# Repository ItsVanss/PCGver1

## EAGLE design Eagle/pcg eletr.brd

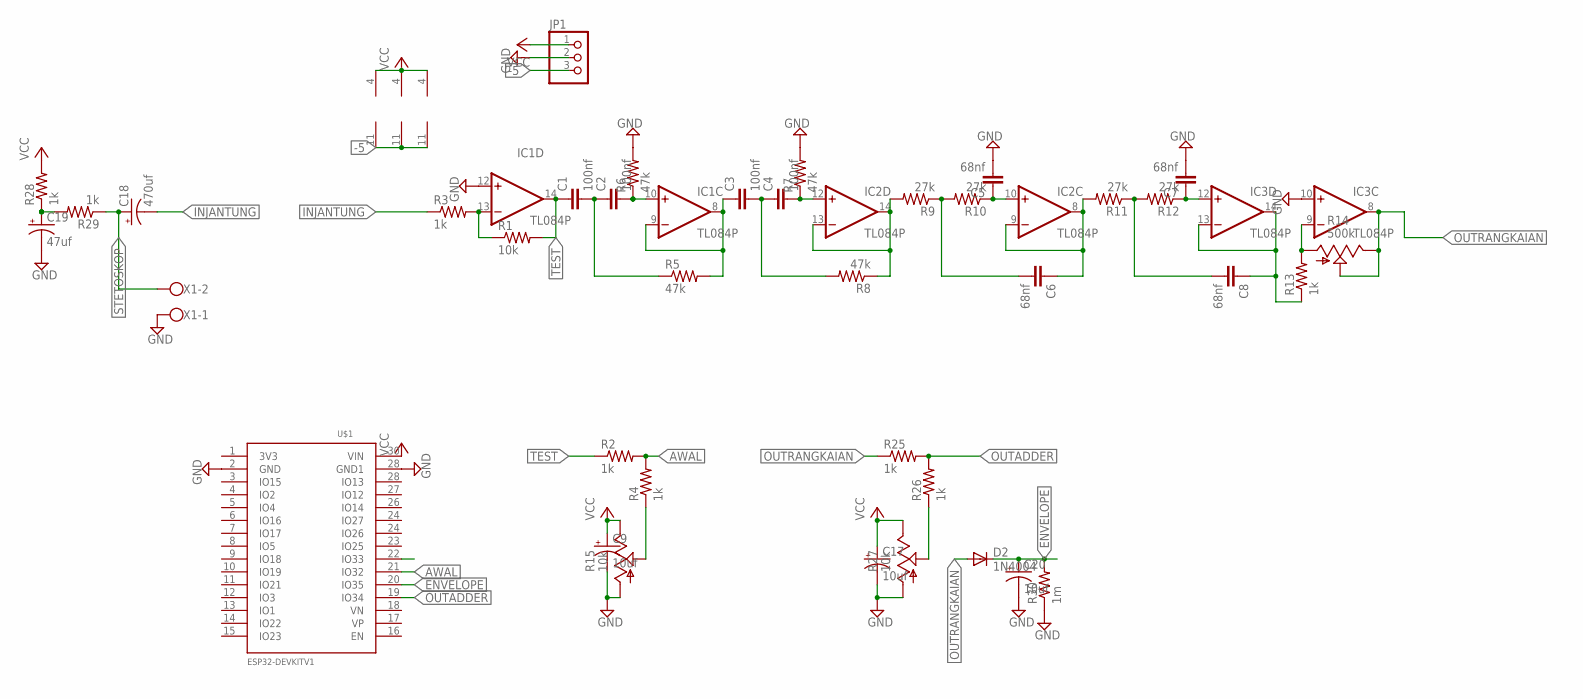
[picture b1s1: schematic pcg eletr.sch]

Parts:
C1, C2, C3, C4: 100nf; C050-025X075
C5, C6, C7, C8: 68nf; C050-025X075
C9, C17, C20: 10uf; E2-5
C18: 470uf; E2,5-7
C19: 47uf; E2-5
D2: 1N4004; DO41-10
IC1, IC2, IC3: TL084P; DIL14
JP1: PINHD-1X3; 1X03
R1: 10k; 0207/7
R2, R3, R4, R13, R25, R26, R28, R29: 1k; 0207/7
R5, R6, R7, R8: 47k; 0207/7
R9, R10, R11, R12: 27k; 0207/7
R14: 500k; B64Y
R15, R27: 10k; B64Y
R30: 1m; 0207/7
U$1: ESP32DEVKITV1; ESP32-DEVKITV1
X1: W237-102

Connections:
-5: IC1.11 (V-), IC2.11 (V-), IC3.11 (V-), JP1.3
AWAL: R2.2, R4.2, U$1.21 (IO32)
ENVELOPE: C20.+, D2.C, R30.2, U$1.20 (IO35)
GND: C5.2, C7.2, C9.-, C17.-, C19.-, C20.-, IC1.12 (+IN), IC3.10 (+IN), JP1.2, R6.2, R7.2, R15.A, R27.A, R30.1, U$1.2 (GND), U$1.28 (IO13), X1.1
INJANTUNG: C18.-, R3.1
unnamed: IC1.13 (-IN), R1.1, R3.2
unnamed: R4.1, R15.S
unnamed: C1.2, C2.1, R5.1
unnamed: C2.2, IC1.10 (+IN), R6.1
unnamed: C3.1, IC1.8 (OUT), IC1.9 (-IN), R5.2
unnamed: C3.2, C4.1, R8.2
unnamed: C4.2, IC2.12 (+IN), R7.1
unnamed: IC2.13 (-IN), IC2.14 (OUT), R8.1, R9.2
unnamed: C6.2, R9.1, R10.2
unnamed: C5.1, IC2.10 (+IN), R10.1
unnamed: C6.1, IC2.8 (OUT), IC2.9 (-IN), R11.2
unnamed: C8.2, R11.1, R12.2
unnamed: C7.1, IC3.12 (+IN), R12.1
unnamed: C8.1, IC3.13 (-IN), IC3.14 (OUT), R13.1
unnamed: IC3.9 (-IN), R13.2, R14.A
unnamed: R26.1, R27.S
unnamed: C19.+, R28.1, R29.2
OUTADDER: R25.2, R26.2, U$1.19 (IO34)
OUTRANGKAIAN: D2.A, IC3.8 (OUT), R14.E, R14.S, R25.1
STETOSKOP: C18.+, R29.1, X1.2
TEST: C1.1, IC1.14 (OUT), R1.2, R2.1
VCC: C9.+, C17.+, IC1.4 (V+), IC2.4 (V+), IC3.4 (V+), JP1.1, R15.E, R27.E, R28.2, U$1.30 (VIN)

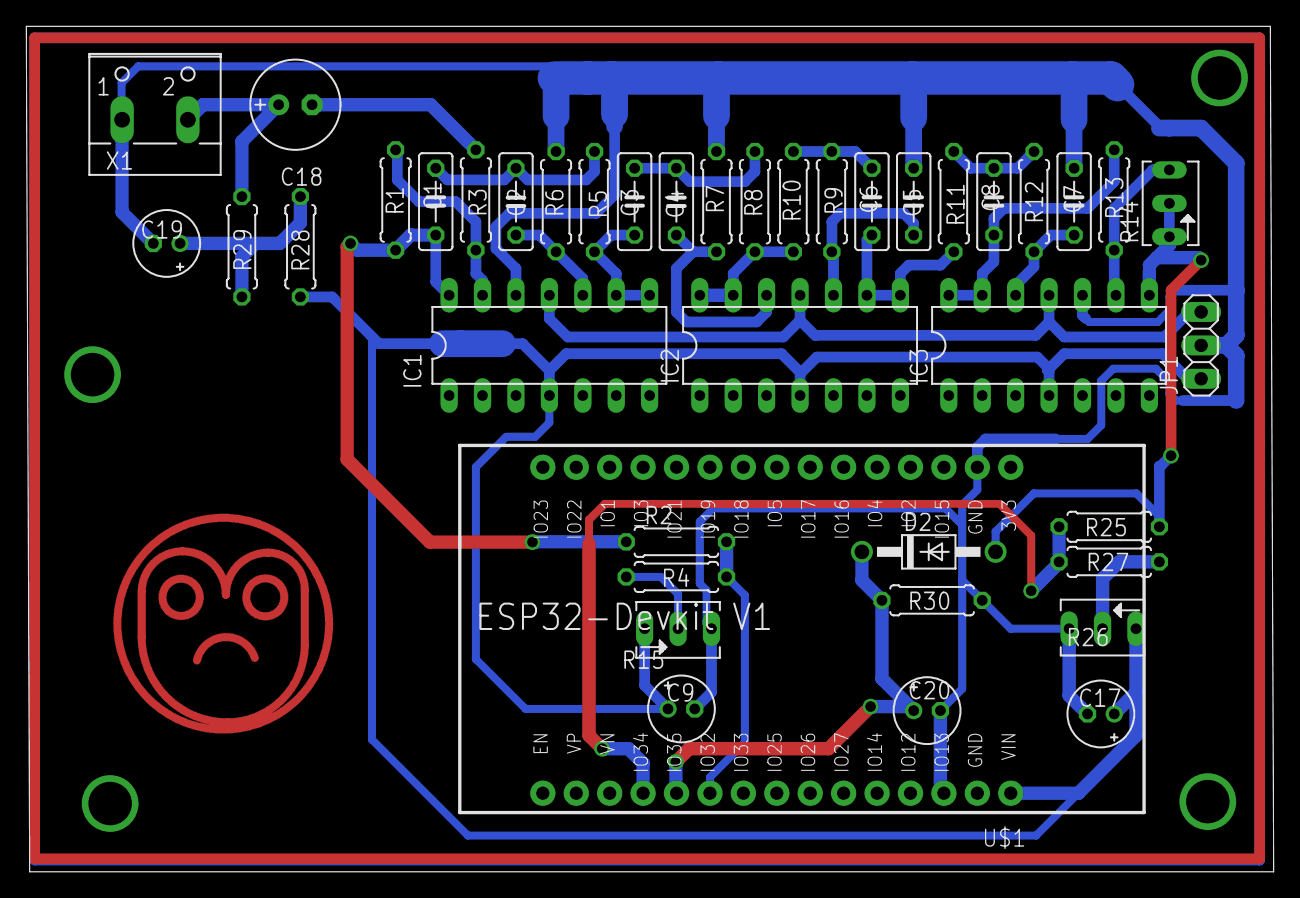
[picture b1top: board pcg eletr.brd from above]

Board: 2 copper layers, 94.8 x 64.3 mm, 41 parts (0 on the bottom side), 27 nets.

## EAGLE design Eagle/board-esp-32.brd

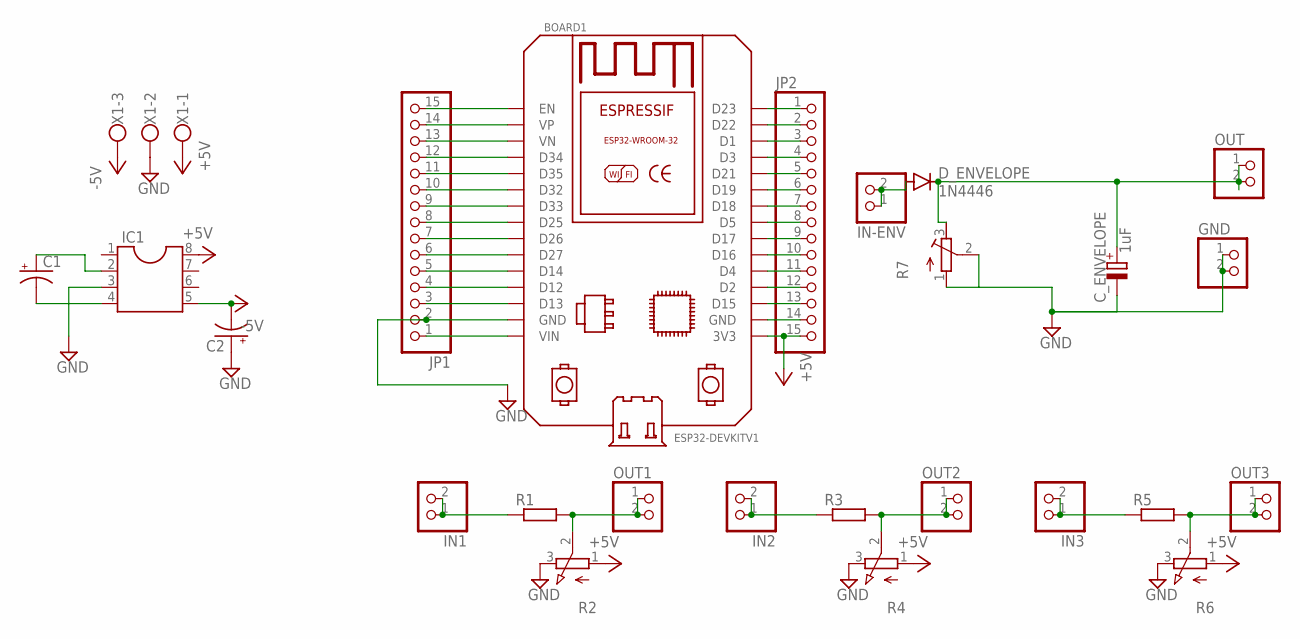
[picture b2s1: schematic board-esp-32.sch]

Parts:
BOARD1: ESP32DEVKITV1; ESP32-DEVKITV1
C1, C2: CPOL-USE2.5-5; E2,5-5
C_ENVELOPE: 1uF; E2,5-6
D_ENVELOPE: 1N4446; DO35-10
GND: PINHD-1X2; 1X02
IC1: DIL8S; SOCKET-08
IN1, IN2, IN3: PINHD-1X2; 1X02
IN-ENV: PINHD-1X2; 1X02
JP1, JP2: PINHD-1X15; 1X15
OUT, OUT1, OUT2, OUT3: PINHD-1X2; 1X02
R1, R3, R5: R-EU_0207/10; 0207/10
R2, R4, R6: 3RP/1610N
R7: R-TRIMM3339P; RTRIM3339P
X1: W237-103

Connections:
+5V: BOARD1.3V3, IC1.8, JP2.15, R2.1 (A), R4.1 (A), R6.1 (A), X1.1
-5V: C2.-, IC1.5, X1.3
GND: BOARD1.GND, C2.+, C_ENVELOPE.-, GND.1, GND.2, IC1.3, JP1.2, R2.3 (E), R4.3 (E), R6.3 (E), R7.1 (A), R7.2 (S), X1.2
unnamed: IN1.1, IN1.2, R1.1
unnamed: OUT1.1, OUT1.2, R1.2, R2.2 (S)
unnamed: IN2.1, IN2.2, R3.1
unnamed: OUT2.1, OUT2.2, R3.2, R4.2 (S)
unnamed: IN3.1, IN3.2, R5.1
unnamed: OUT3.1, OUT3.2, R5.2, R6.2 (S)
unnamed: BOARD1.GND@1 (GND), JP2.14
unnamed: C1.+, IC1.2
unnamed: C1.-, IC1.4
unnamed: BOARD1.D15, JP2.13
unnamed: BOARD1.D2, JP2.12
unnamed: BOARD1.D4, JP2.11
unnamed: BOARD1.D16, JP2.10
unnamed: BOARD1.D17, JP2.9
unnamed: BOARD1.D5, JP2.8
unnamed: C_ENVELOPE.+, D_ENVELOPE.C, OUT.1, OUT.2, R7.3 (E)
unnamed: D_ENVELOPE.A, IN-ENV.1, IN-ENV.2
unnamed: BOARD1.D18, JP2.7
unnamed: BOARD1.D19, JP2.6
unnamed: BOARD1.D21, JP2.5
unnamed: BOARD1.D3, JP2.4
unnamed: BOARD1.D1, JP2.3
unnamed: BOARD1.D22, JP2.2
unnamed: BOARD1.D23, JP2.1
unnamed: BOARD1.EN, JP1.15
unnamed: BOARD1.VP, JP1.14
unnamed: BOARD1.VN, JP1.13
unnamed: BOARD1.D34, JP1.12
unnamed: BOARD1.D35, JP1.11
unnamed: BOARD1.D32, JP1.10
unnamed: BOARD1.D33, JP1.9
unnamed: BOARD1.D25, JP1.8
unnamed: BOARD1.D26, JP1.7
unnamed: BOARD1.D27, JP1.6
unnamed: BOARD1.D14, JP1.5
unnamed: BOARD1.D12, JP1.4
unnamed: BOARD1.D13, JP1.3
unnamed: BOARD1.VIN, JP1.1

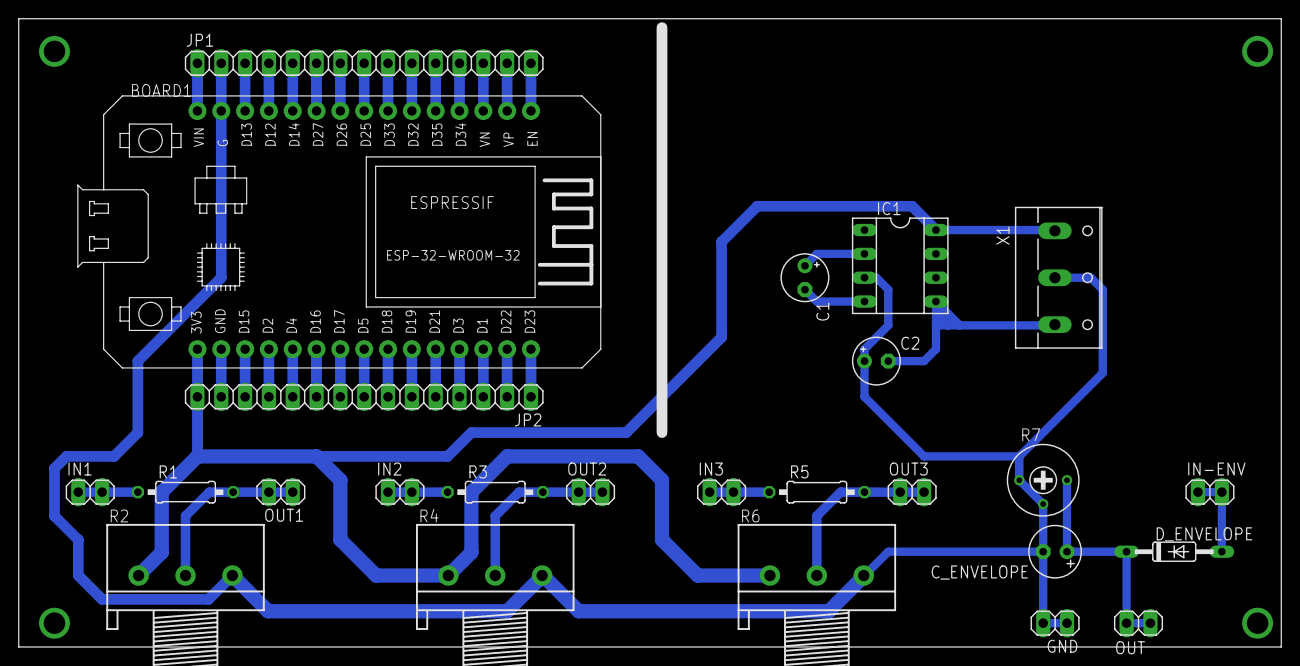
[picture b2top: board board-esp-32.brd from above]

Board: 2 copper layers, 134.6 x 67.0 mm, 25 parts (0 on the bottom side), 41 nets.

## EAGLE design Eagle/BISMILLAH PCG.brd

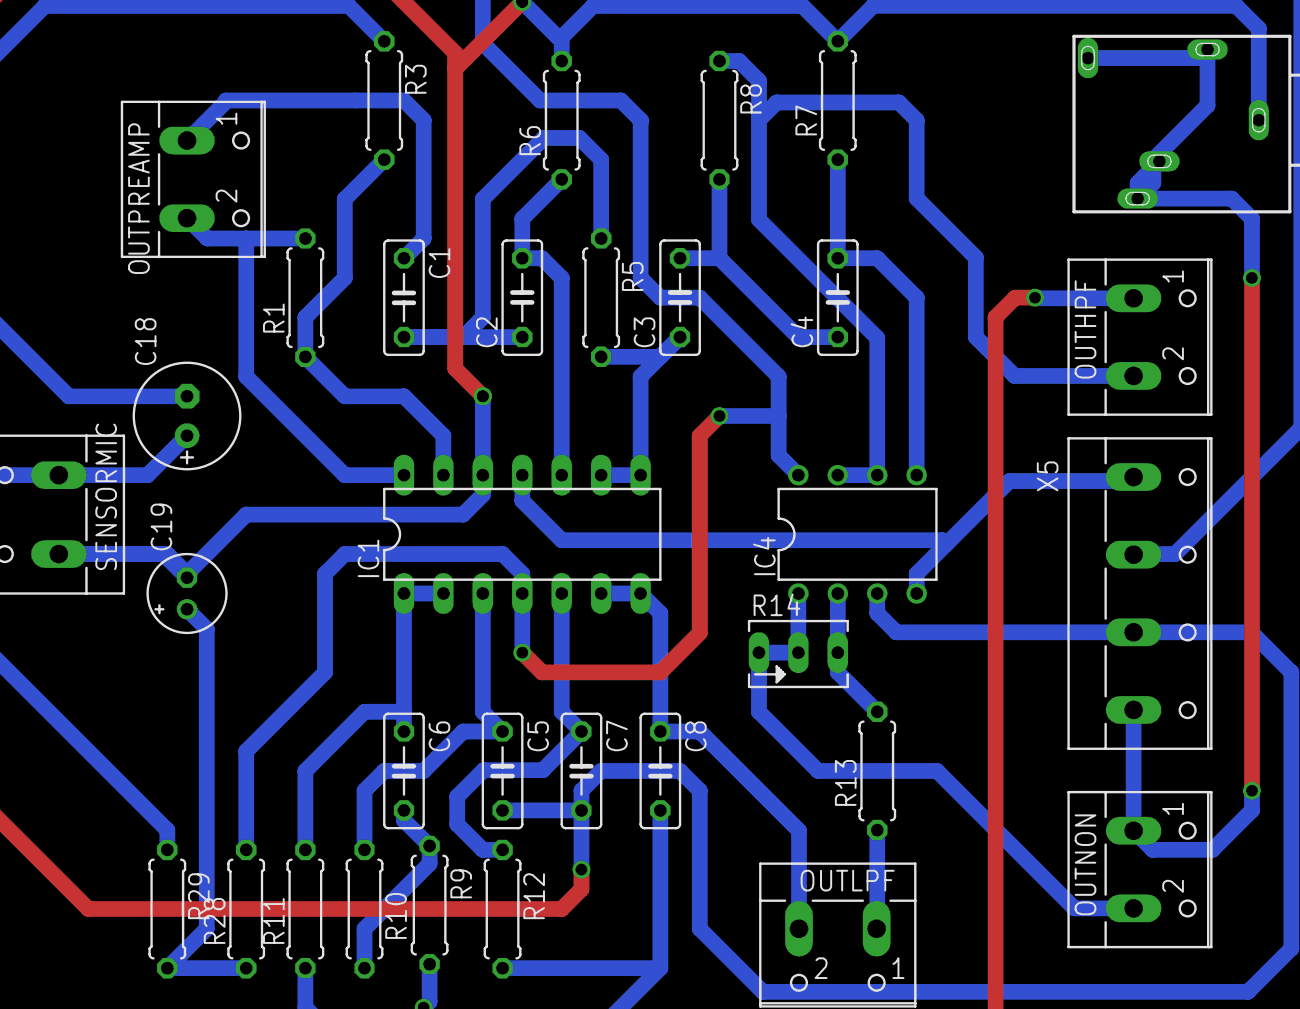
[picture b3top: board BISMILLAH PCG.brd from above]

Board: 2 copper layers, 33 parts (0 on the bottom side), 26 nets.

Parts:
C1, C2, C3, C4: 100nf; C050-025X075
C5, C6, C7, C8: 68nf; C050-025X075
C18: 470uf; E2,5-7
C19: 47uf; E2-5
HEADSET: headset; 1503_09
IC1: TL084P; DIL14
IC4: TL082P; DIL08
OUTHPF: W237-102
OUTLPF: W237-102
OUTNON: W237-102
OUTPREAMP: W237-102
R1: 10k; 0207/7
R3, R13, R28, R29: 1k; 0207/7
R5, R6, R7, R8: 47k; 0207/7
R9, R10, R11, R12: 27k; 0207/7
R14: 500k; B64Y
SENSORMIC: W237-132
X5: W237-4

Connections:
GND: C5.2, C7.2, C19.-, HEADSET.1, IC1.12, IC4.3, R6.2, R7.2, SENSORMIC.1, X5.3
unnamed: IC1.13, R1.1, R3.2
unnamed: IC1.14, OUTPREAMP.2, R1.2
unnamed: C18.-, R3.1
unnamed: C1.1, OUTPREAMP.1
unnamed: IC4.1, OUTNON.2, R14.E, R14.S
unnamed: C1.2, C2.1, R5.1
unnamed: C2.2, IC1.10, R6.1
unnamed: C3.1, IC1.8, IC1.9, R5.2
unnamed: C3.2, C4.1, R8.2
unnamed: C4.2, IC4.5, R7.1
unnamed: IC4.6, IC4.7, OUTHPF.2, R8.1
unnamed: C6.2, R9.1, R10.2
unnamed: C5.1, IC1.3, R10.1
unnamed: C6.1, IC1.1, IC1.2, R11.2
unnamed: C8.2, R11.1, R12.2
unnamed: C7.1, IC1.5, R12.1
unnamed: C8.1, IC1.6, IC1.7, OUTLPF.2
unnamed: IC4.2, R13.2, R14.A
unnamed: OUTHPF.1, R9.2
unnamed: OUTLPF.1, R13.1
unnamed: C19.+, R28.1, R29.2
OUTJANTUNG: HEADSET.2, HEADSET.3, HEADSET.4, HEADSET.5, OUTNON.1, X5.4
STETOSKOP1: C18.+, R29.1, SENSORMIC.2
V-: IC1.11, IC4.4, X5.1
VCC: IC1.4, IC4.8, R28.2, X5.2

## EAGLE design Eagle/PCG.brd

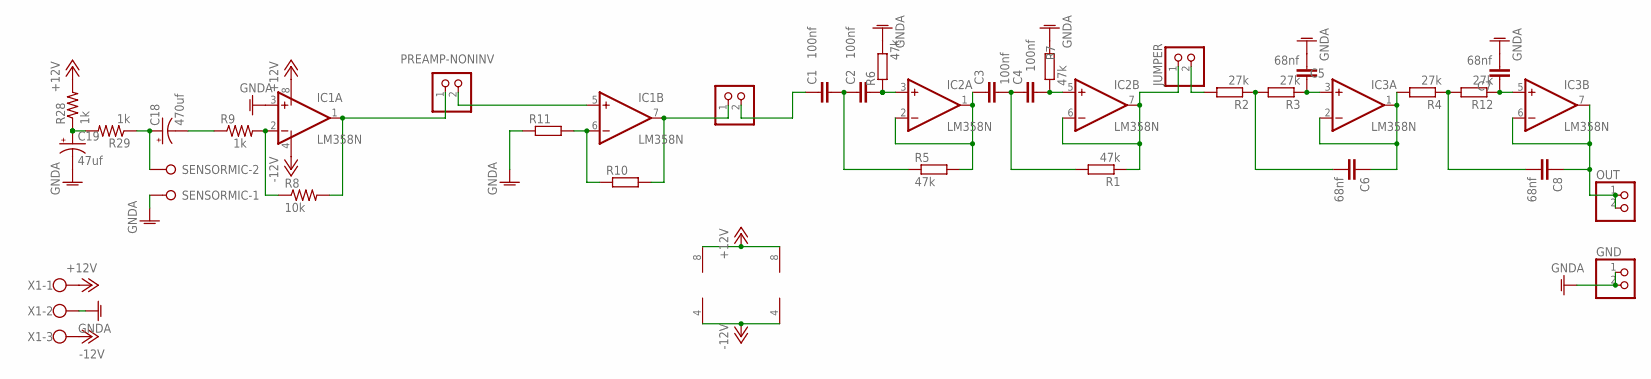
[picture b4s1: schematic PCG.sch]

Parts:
C1, C2, C3, C4: 100nf; C050-025X075
C5, C6, C7, C8: 68nf; C050-025X075
C18: 470uf; E2,5-7
C19: 47uf; E2-5
GND: PINHD-1X2; 1X02
IC1, IC2, IC3: LM358N; DIL08
JUMPER: PINHD-1X2; 1X02
NONINV-BPF: PINHD-1X2; 1X02
OUT: PINHD-1X2; 1X02
PREAMP-NONINV: PINHD-1X2; 1X02
R1, R5, R6, R7: 47k; 0207/10
R2, R3, R4, R12: 27k; 0207/10
R8: 10k; 0207/7
R9, R28, R29: 1k; 0207/7
R10, R11: R-EU_0207/10; 0207/10
SENSORMIC: W237-02P; W237-132
X1: W237-103

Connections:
+12V: IC1.8 (V+), IC2.8 (V+), IC3.8 (V+), R28.2, X1.1
-12V: IC1.4 (V-), IC2.4 (V-), IC3.4 (V-), X1.3
GNDA: C5.2, C7.2, C19.-, GND.1, GND.2, IC1.3 (+IN), R6.2, R7.2, R11.1, SENSORMIC.1, X1.2
unnamed: C2.2, IC2.3 (+IN), R6.1
unnamed: C7.1, IC3.5 (+IN), R12.1
unnamed: C8.1, IC3.6 (-IN), IC3.7 (OUT), OUT.1, OUT.2
unnamed: JUMPER.2, R2.2
unnamed: C1.2, C2.1, R5.1
unnamed: C1.1, NONINV-BPF.2
unnamed: C3.1, IC2.1 (OUT), IC2.2 (-IN), R5.2
unnamed: C3.2, C4.1, R1.2
unnamed: C4.2, IC2.5 (+IN), R7.1
unnamed: IC2.6 (-IN), IC2.7 (OUT), JUMPER.1, R1.1
unnamed: C6.2, R2.1, R3.2
unnamed: C5.1, IC3.3 (+IN), R3.1
unnamed: C6.1, IC3.1 (OUT), IC3.2 (-IN), R4.2
unnamed: C8.2, R4.1, R12.2
unnamed: IC1.2 (-IN), R8.1, R9.2
unnamed: IC1.1 (OUT), PREAMP-NONINV.1, R8.2
unnamed: C18.-, R9.1
unnamed: IC1.6 (-IN), R10.1, R11.2
unnamed: IC1.7 (OUT), NONINV-BPF.1, R10.2
unnamed: IC1.5 (+IN), PREAMP-NONINV.2
unnamed: C19.+, R28.1, R29.2
STETOSKOP1: C18.+, R29.1, SENSORMIC.2

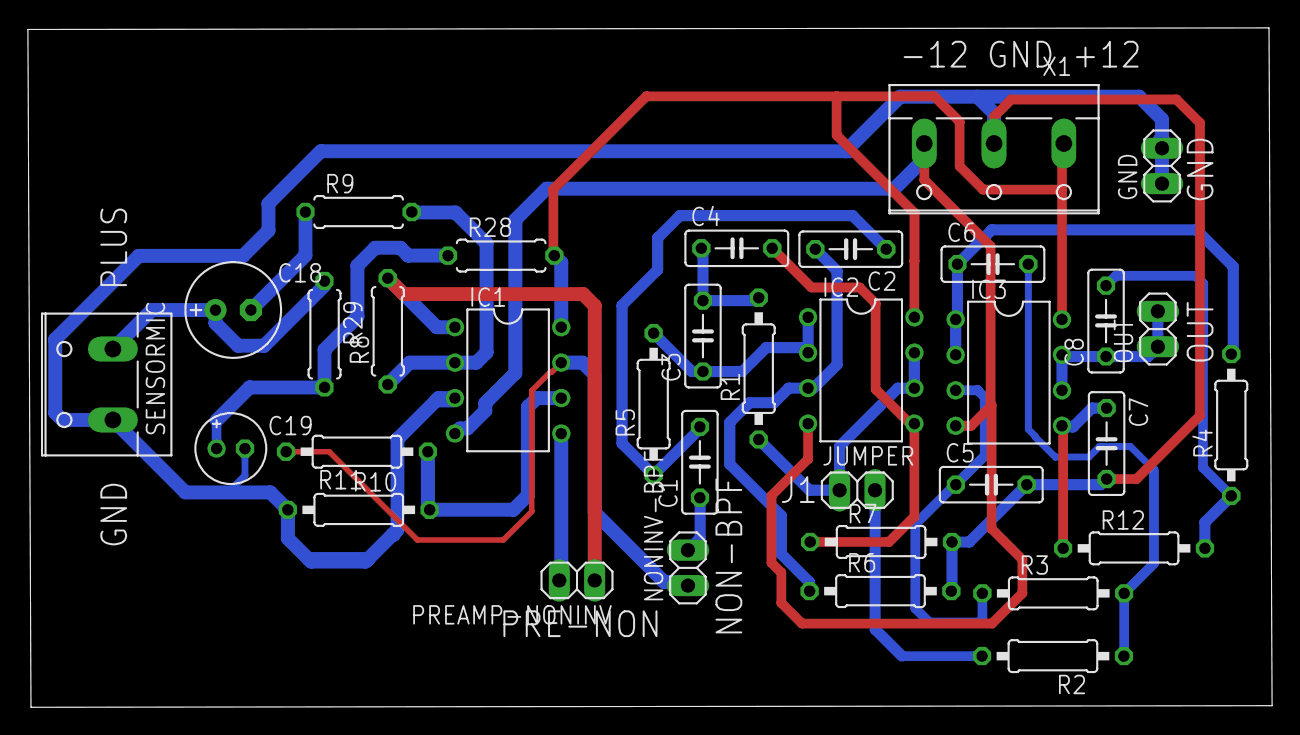
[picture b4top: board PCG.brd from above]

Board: 2 copper layers, 89.2 x 48.7 mm, 34 parts (0 on the bottom side), 25 nets.

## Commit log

2025-10-07 Second Commit
2025-10-13 Thrid Commit
2025-10-15 Fourth Commit
2025-10-16 Another Commit 5
2025-10-16 Another Commit 6
